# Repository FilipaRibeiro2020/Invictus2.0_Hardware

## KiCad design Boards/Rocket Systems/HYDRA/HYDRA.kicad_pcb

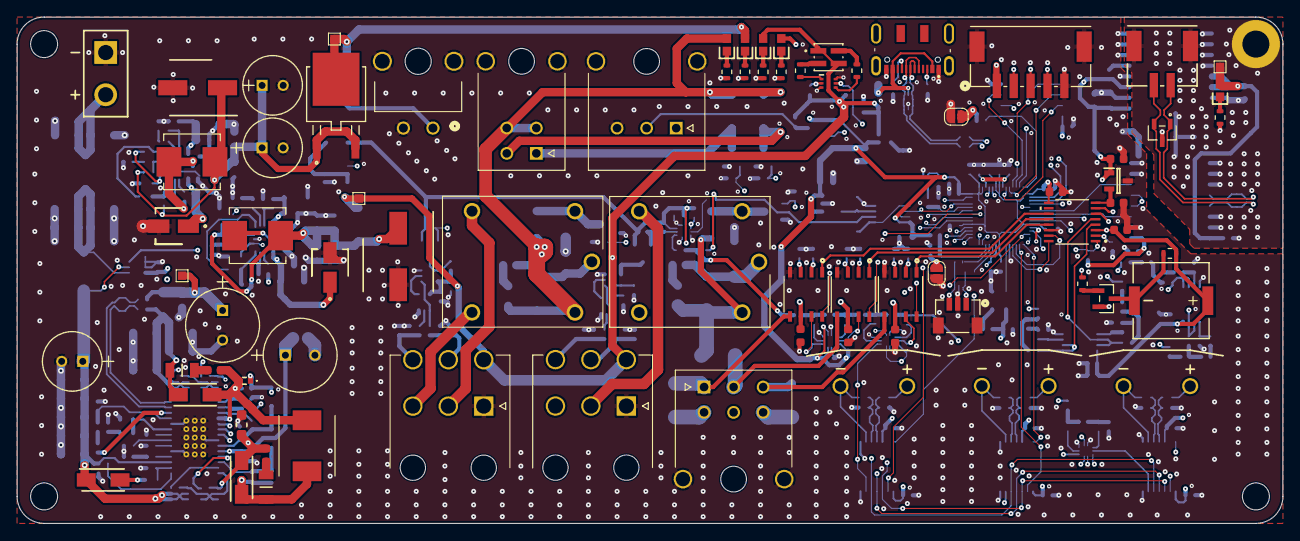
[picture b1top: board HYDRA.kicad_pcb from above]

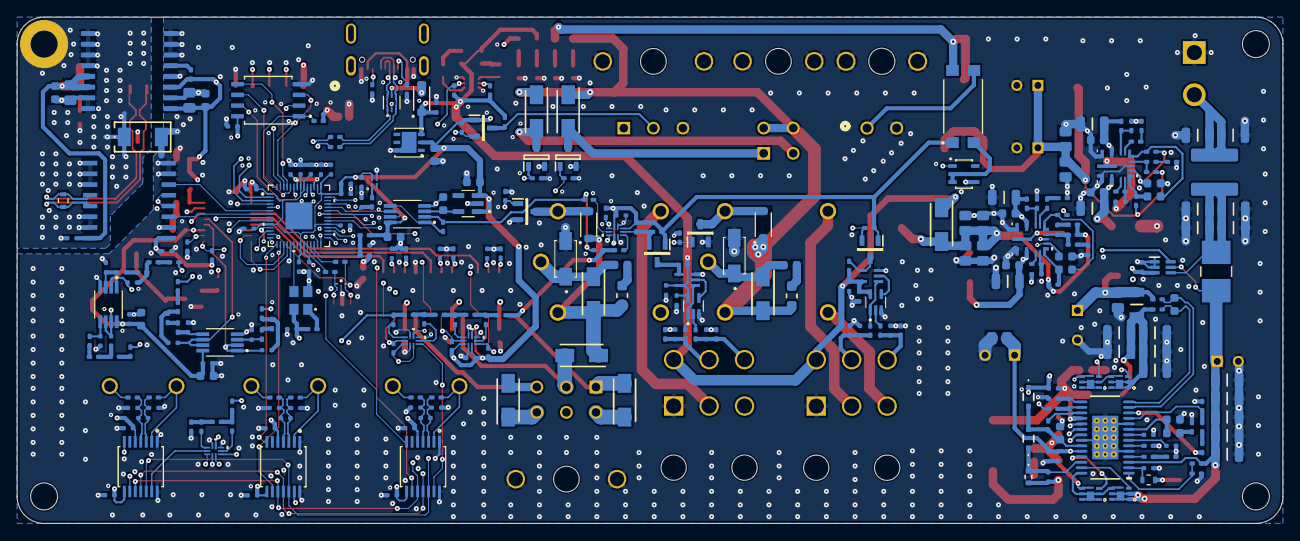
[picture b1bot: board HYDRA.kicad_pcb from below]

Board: 6 copper layers, 150.0 x 60.0 mm, 381 parts (302 on the bottom side), 234 nets.

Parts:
C1, C3, C6, C13: 1uF; Capacitor_0402
C1_comp1: 22nF; Capacitor_0603
C2, C4, C5, C7, C8, C9, C10, C11, C12, C14, C17, C62: 100nF; Capacitor_0402
C2_comp1: 270pF; Capacitor_0603
C15, C18, C20, C22, C23, C24, C25, C26, C27, C28, C30, C32, C33, C34, C36, C37, C41, C43, C44, C51, C54, C55, C57, C64, C66, C93, C94, C95: 100n; Capacitor_0402
C16: 4.7uF; Capacitor_0603
C19, C21, C29, C31, C40, C42, C45, C46, C47, C48: 10n; Capacitor_0402
C35, C38, C39, C56, C58, C60, C61, C63, C65: 1u; Capacitor_0603
C49, C50, C52, C53: 4.7n; Capacitor_0402
C59: 470n; Capacitor_0402
C67, C69, C72, C74: 2.2u; Capacitor_1206
C68: 68uF; CAP_WCAP-ATG8_6.3x11_WRE
C70, C71, C73, C75, C77: 4.7uF; Capacitor_1206
C76, C78: 470n; Capacitor_1206
C79, C88: 10uF; Capacitor_0805
C80, C86: 100nF; Capacitor_0603
C81: 300pF; C1808
C82, C83, C84, C85, C87: 10uF; Capacitor_1206
C89, C92: 3.3uF; Capacitor_0805
C90, C91: 180uF; CAP_WCAP-ATG8_8x11.5_WRE
C96, C97, C98: 1uF; Capacitor_0603
C99, C100: 100n; Capacitor_0603
CR1, CR2, CR3, CR4, CR5: VLMY1300-GS08; LEDC1608X100N
CR6: SP712-02HTG; SOT23-3_LTF
C_BIAS1, C_BIAS3: 1u; Capacitor_0603
C_BT1, C_BT2: 100n; Capacitor_0402
C_Boot2: 100nF; Capacitor_0402
C_FF1: 22p; Capacitor_0402
C_IN1, C_IN2, C_IN3, C_IN4: 4.7u; Capacitor_1206
C_IN-BLK1, C_IN-BLK2: 10u; Capacitor_4mm
C_IN_HFI1, C_IN_HFI2, C_IN_HFI3, C_IN_HFI4: 100n; Capacitor_0603
C_OUT1, C_OUT2, C_OUT6, C_OUT7, C_OUT8, C_OUT9: 22u; Capacitor_0805
C_OUT3, C_OUT4: 47u; CAP_WCAP-ATG8_6.3x11_WRE
C_OUT5: 100u; Capacitor-6.3mm
C_OUT10: 560u; Capacitor_8mm
C_Q1, C_Q2: 100pF; Capacitor_0603
C_VCC1, C_VCC3: 1u; Capacitor_0603
C_VIN1: 100nF; Capacitor_0402
C_bias2: 100nF; Capacitor_0402
C_boot1: 100nF; Capacitor_0402
C_cs1: 47pF; Capacitor_0402
C_isns1: 1uF; Capacitor_0603
C_slope1: 100pF; Capacitor_0402
C_ss1: 100nF; Capacitor_0402
C_vcc2: 1uF; Capacitor_0603
C_vosns1: 100pF; Capacitor_0402
D1: ESD122DMYR; DIO_ESD122DMYR
D2: SP3004-04XTG; SOT563_LTF
D3, D13, D14: PMEG2010ER; SODFL3517X110N
D4, D6, D7, D8, D9, D10, D11, D12, D17, D18, D19: RSX301L; DIOM5026X220N
D15, D16: SMAJ12A; DIOM4325X250N
D_Boot1, D_Boot2: BAS316,115; BAS316115
H1, H2, H4: MountingHole; MountingHole_3.2mm_M3_ISO7380
H3: MountingHole_Pad; MountingHole_3.2mm_M3_ISO7380_Pad
IC1: NSVT30010MXV6T1G; SOTFL50P160X60-6N
IC2: INA181A3QDCKRQ1; SOT65P210X110-6N
IC3: ISL21010CFH325Z-TK; SOT95P237X112-3N
J1: BM03B-SRSS-TBLFSN; CONN_BM03B-SRSS-TBLFSN_JST
J2: DX07S016JA1R1500; JAE_DX07S016JA1R1500
J3, J4: 26013116; MOLEX_26013116
J5: XT30UPB-F; XT30UPBF
J6: 5024430270; CONN_502443-02xx_MOL
J7: 1723163206; MOLEX_1723163206
J8: 1723163304; MOLEX_1723163304
J9: 1723103102; CONN02_1723103102_MOL
J10: 1723103103; MOLEX_1723103103
J11: 5024430570; CONN_502443-05xx_MOL
JP1, JP2: Jumper_2_Open; SolderJumper-2_P1.3mm_Open_RoundedPad1.0x1.5mm
K1: G3VM-31DR_TR05_; G3VM31DRTR05
K2, K3: PR12-12V-360-1C; RELAY_PR12-12V-360-1C
L1: 2.2u; SRP6030CA-2R2M
LS1: PKMCS0909E4000-R1; SPKR_PKMCS0909E4000-R1
L_SW1: 10u; Inductor-7.3mm-10u
L_SW2: 4.7uH; Inductor-7.2mm-4u7
L_SW3: 10uH; Inductor-7.3mm-10u
MCU1: RP2040; QFN56_7X7_RPI
Q1, Q2, Q7, Q8, Q9: BSS123; SOT96P237X111-3N
Q3, Q4, Q5, Q6: IRLHS6242TRPBF; QFN65P200X200X100-8N
Q10, Q11: PMV20XNER; SOT95P230X110-3N
R1: 62; RES_0603
R1_fb1: 20k; RES_0402
R1_mode1: 91k; RES_0402
R2, R3: 150; RES_0603
R2_fb1: 280k; RES_0402
R2_mode1, R24, R25, R26, R27, R32, R33, R35, R37, R40, R41, R46, R48, R50, R52: 2k; RES_0402
R3_fb1: 10; RES_0402
R4: 320; RES_0603
R5: 500; RES_0603
R6, R9, R18, R28, R29, R38, R45, R53, R54, R58, R61, R85, R86: 10k; RES_0402
R7, R8: 100; RES_0603
R10, R11: 1k; RES_0603
R12, R17, R21, R30, R31, R34, R36, R39, R42, R47, R49, R51, R55, R56, R57, R78: 1k; RES_0402
R13, R14: 27; RES_0402
R15, R16, R22, R23, R43, R44, R59, R60: 100; RES_0402
R19, R20: 5k1; RES_0402
R62, R63, R64, R66, R67, R68: 3k; RES_0402
R65, R69: 1k8; RES_0402
R70, R71, R72: 24k; RES_0402
R73: 5k6; RES_0402
R74, R75, R76: 750; RES_0402
R77: 36k; RES_0402
R79, R87, R88, R89, R92: 100k; RES_0402
R80: 120; RES_0603
R81: 100K; RES_0402
R82, R83, R84: 205K; RES_0402
R90, R91: 1k; RES_0805
R_BIAS1, R_BIAS2: 5; RES_0402
R_BT1: 50; RES_0402
R_BT2: 100; RES_0402
R_EN1: 390k; RES_0402
R_EN2: 56k; RES_0402
R_ENB1: 110k; RES_0402
R_ENB2: 56k; RES_0402
R_ENT1: 910k; RES_0402
R_ENT2: 470k; RES_0402
R_FBB1: 22k; RES_0402
R_FBB2: 100; RES_0402
R_FBT1: 12k; RES_0402
R_FBT2: 620; RES_0402
R_FBT3, R_FBT4: 100K; RES_0402
R_FF1: 1k; RES_0402
R_PG1, R_PG2: 100K; RES_0402
R_Q1, R_Q2: 10; RES_1206
R_RT1, R_RT3: 33k; RES_0402
R_RT2, R_RT4: 200; RES_0402
R_SENSE2: 8m; RES_2512
R_SNS1: 10m; RES_1206
R_VIN1: 10; RES_0603
R_comp1: 10k; RES_0402
R_cs1: 100; RES_0402
R_csg1: 100; RES_0402
R_good1: 10k; RES_0402
R_isns+1: 100; RES_0402
R_isns-1: 100; RES_0402
R_sense1: 8m; RES_0805
R_sync1: 84k5; RES_0402
TP2, TP3, TP5, TP6: TestPoint; TestPoint_Pad_1.0x1.0mm
U1: VLMKG3400-GS08; SMT_00-GS08_VIS
U2: BC846BLT1G; SOT-23_ONS
U3: W25Q128JVSIQ TR; SOIC_208MIL_WIN
U4: ST1L05APU33R; DFN_5APU33R_STM
U5, U6, U10, U11: NLAS5223BMNR2G; WQFN10_1P4X1P8_ONS
U7, U12, U16: MAX31856MUD+T; 21-0066J_14_MXM
U8, U15: SN74AHC1G86DCKRE4; SOT65P210X110-5N
U9, U17: 74AHC1G08SE-7; SOT65P210X110-5N
U13, U18, U19: MCP6002-E/MS; MSOP8_MC_MCH
U14: NCV8114ASN165T1G; SOT95P275X120-5N
U20: STLM20DD9F; UDFN-4L_STM
U21: AD5593RBRUZ; RU-16_ADI-L
U22: ISO1410BDW; DW0016B_L
U23, U25: LM61460AASQRJRRQ1; VQFN-HR14_RJR_TEX
U24: LM5175PWPR; PWP0028F_L
U26: UCC12050DVE; DVE0016A
U27: NCR321UX; TSOP6_SOT457_NEX
U28, U29, U30: DRV103H; DDA8-L
U31, U32, U33: ThermoConnector; Thermo Type K PCB Connector
U34: STPS15L45CB; DPAK_STM
XTAL1: ASE-12.000MHZ-LC-T; ASE24576MHZLCT
Z_Boot1, Z_Boot2: BZT52C8V2T-7; BZT52C8V2T7

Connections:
+1.65V: C39.1, U13.3 (VINA+), U14.5 (OUT)
+2.5V: C63.1, IC3.2 (VOUT), U21.8 (VREF)
+3.3V: C5.1, C6.1, C7.1, C8.1, C9.1, C10.1, C11.1, C12.1, C13.1, C14.1, C16.2, C17.1, C24.1, C25.1, C26.1, C27.2, C33.1, C34.2, C35.2, C38.1, C44.1, C51.2, C62.1, C64.1, C65.1, CR1.2, K1.1, MCU1.1 (IOVDD), MCU1.10 (IOVDD), MCU1.22 (IOVDD), MCU1.33 (IOVDD), MCU1.42 (IOVDD), MCU1.43 (ADC_AVDD), MCU1.44 (VREG_IN), MCU1.48 (USB_VDD), MCU1.49 (IOVDD), Q1.1 (G), Q2.1 (G), Q7.1 (G), R12.1, R18.2, R24.1, R25.1, R26.1, R27.1, R41.1, R45.1, R61.1, R79.1, R86.1, U3.8 (VCC), U4.2 (V0), U5.1 (VCC), U5.5 (NC1), U5.7 (NC2), U6.1 (VCC), U6.5 (NC1), U6.7 (NC2), U7.5 (AVDD), U7.8 (DVDD), U10.1 (VCC), U10.5 (NC1), U10.7 (NC2), U11.1 (VCC), U11.5 (NC1), U11.7 (NC2), U12.5 (AVDD), U12.8 (DVDD), U13.8 (VDD), U14.1 (IN), U14.3 (EN), U16.5 (AVDD), U16.8 (DVDD), U20.4 (VCC), U21.9 (VLOGIC), U22.1 (VCC1), XTAL1.4 (VDD)
+5V: C15.1, C18.1, C28.1, C32.1, C43.1, C54.1, C55.2, C56.1, C57.2, C58.1, C60.1, C61.1, C79.1, C80.1, CR3.2, D3.C, D8.1 (K), IC2.3 (VS), IC3.1 (VIN), J3.4, J4.4, LS1.1, R6.1, R9.2, R11.1, R38.1, R58.1, R81.1, R85.1, TP6.1, U1.1 (C_RED), U1.3 (C_Green), U4.3 (V1), U8.5 (VCC), U9.5 (VCC), U15.5 (VCC), U17.5 (VCC), U18.8 (VDD), U19.8 (VDD), U21.3 (VDD), U26.1 (EN), U26.3 (VINP)
+5VA: C66.2, C86.1, C88.1, CR2.2, TP3.1, U22.16 (VCC2), U26.13 (SEL), U26.14 (VISO)
+8.4V: CR4.2, J10.1, K1.4, TP2.1, U34.3 (K)
+12V: C89.2, C90.1, C91.1, C92.2, C96.1, C97.1, C98.1, CR5.2, C_bias2.1, C_vosns1.1, D9.1 (K), D10.1 (K), D11.1 (K), D12.1 (K), D13.C, D14.C, D17.2 (A), D18.2 (A), D19.1 (K), J7.4, J7.5, J7.6, J8.3, J8.4, J11.1, K2.A1, K3.A1, R3_fb1.1, R90.1, R91.1, R_SNS1.2, R_isns-1.1, TP5.1, U24.12 (VOSNS), U24.24 (BIAS), U28.6 (VS+), U29.6 (VS+), U30.6 (VS+)
/1~DRDY THERMO: MCU1.9 (GPIO7), U7.7 (~DRDY)
/2~DRDY THERMO: MCU1.15 (GPIO12), U12.7 (~DRDY)
/3~DRDY THERMO: MCU1.28 (GPIO17), U16.7 (~DRDY)
/Actuation Unit/CAM EN: MCU1.37 (GPIO25), U27.1 (VEN)
/Actuation Unit/CAM IN: J9.1, K1.3
/Actuation Unit/PWM HV: J10.2, Q7.3 (D), R85.2
/Actuation Unit/PWM LV: MCU1.5 (GPIO3), Q7.2 (S), R86.2
/Actuation Unit/QuickDisco N2: MCU1.34 (GPIO22), Q10.1 (G), R89.1
/Actuation Unit/QuickDisco N2 OUT: D12.2 (A), J8.1, Q10.3 (D)
/Actuation Unit/QuickDisco N2O: MCU1.32 (GPIO21), Q11.1 (G), R92.1
/Actuation Unit/QuickDisco N2O OUT: D19.2 (A), J8.2, Q11.3 (D)
/Actuation Unit/SOL_VALVE_1: MCU1.29 (GPIO18), U28.8 (INPUT)
/Actuation Unit/SOL_VALVE_1 DUTY: U21.11 (I/O5), U28.1 (DUTY_CYCLE)
/Actuation Unit/SOL_VALVE_1 OUT: D9.2 (A), J7.1, U28.5 (OUT)
/Actuation Unit/SOL_VALVE_1 ~FAULT: R25.2, U5.8 (IN2), U28.7 (STATUS_OK_FLAG)
/Actuation Unit/SOL_VALVE_2: MCU1.30 (GPIO19), U29.8 (INPUT)
/Actuation Unit/SOL_VALVE_2 DUTY: U21.12 (I/O6), U29.1 (DUTY_CYCLE)
/Actuation Unit/SOL_VALVE_2 OUT: D10.2 (A), J7.2, U29.5 (OUT)
/Actuation Unit/SOL_VALVE_2 ~FAULT: R24.2, U5.4 (IN1), U29.7 (STATUS_OK_FLAG)
/Actuation Unit/SOL_VALVE_3: MCU1.31 (GPIO20), U30.8 (INPUT)
/Actuation Unit/SOL_VALVE_3 DUTY: U21.13 (I/O7), U30.1 (DUTY_CYCLE)
/Actuation Unit/SOL_VALVE_3 OUT: D11.2 (A), J7.3, U30.5 (OUT)
/Actuation Unit/SOL_VALVE_3 ~FAULT: R41.2, U11.4 (IN1), U30.7 (STATUS_OK_FLAG)
/Actuation Unit/STVALVE_1: MCU1.35 (GPIO23), Q8.1 (G), R87.1
/Actuation Unit/STVALVE_1_CLOSED: J4.2, K3.NO
/Actuation Unit/STVALVE_1_OPEN: J4.3, K3.NC
/Actuation Unit/STVALVE_2: MCU1.36 (GPIO24), Q9.1 (G), R88.1
/Actuation Unit/STVALVE_2_CLOSED: J3.2, K2.NO
/Actuation Unit/STVALVE_2_OPEN: J3.3, K2.NC
/Buzzer: MCU1.4 (GPIO2), R10.2
/ENABLE_RS: MCU1.8 (GPIO6), U22.4 (~RE), U22.5 (DE)
/IO Connectors/PRESSURE1 Sense: J11.2, R62.1
/IO Connectors/PRESSURE2 Sense: J11.3, R63.1
/IO Connectors/PRESSURE3 Sense: J11.4, R64.1
/IO Connectors/RS_DN: CR6.1, J6.2, R80.1, U22.12 (A)
/IO Connectors/RS_DP: CR6.2, J6.1, R80.2, U22.13 (B)
/IO Connectors/SBVALVE_1_T2: C23.1, J4.6, R29.1, R31.2
/IO Connectors/SBVALVE_1_T3: C22.1, J4.5, R28.1, R30.2
/IO Connectors/SBVALVE_2_T2: C37.1, J3.6, R54.1, R57.2
/IO Connectors/SBVALVE_2_T3: C36.1, J3.5, R53.1, R56.2
/IO Connectors/THERMO1 DN: R23.2, U7.2 (BIAS), U31.2 (T-)
/IO Connectors/THERMO1 DP: R22.2, U31.1 (T+)
/IO Connectors/THERMO2 DN: R44.2, U12.2 (BIAS), U32.2 (T-)
/IO Connectors/THERMO2 DP: R43.2, U32.1 (T+)
/IO Connectors/THERMO3 DN: R60.2, U16.2 (BIAS), U33.2 (T-)
/IO Connectors/THERMO3 DP: R59.2, U33.1 (T+)
/MISO SPI: MCU1.11 (GPIO8), U7.11 (SDO), U12.11 (SDO), U16.11 (SDO)
/MOSI SPI: MCU1.14 (GPIO11), U7.12 (SDI), U12.12 (SDI), U16.12 (SDI)
/PCB Temperature Sense: C59.2, MCU1.38 (GPIO26_ADC0), R77.1
/Power Unit/DC.DC2 PGOOD: C_BIAS1.2, R_PG1.2, U23.5 (PGOOD)
/Power Unit/DC.DC2 VCC: C_VCC1.1, R_PG1.1, U23.2 (VCC)
/Power Unit/DC.DC3 PGOOD: C_BIAS3.2, R_PG2.2, U25.5 (PGOOD)
/Power Unit/DC.DC3 VCC: C_VCC3.1, R_PG2.1, U25.2 (VCC)
/Power Unit/HDRV1: Q3.3, U24.27 (HDRV1)
/Power Unit/HDRV2: Q5.3, U24.19 (HDRV2)
/Power Unit/ISNS+: C_isns1.2, R_isns+1.2, U24.14 (ISNS+)
/Power Unit/ISNS-: C_isns1.1, R_isns-1.2, U24.13 (ISNS-)
/Power Unit/LDRV1: Q4.3, U24.25 (LDRV1)
/Power Unit/LDRV2: Q6.3, U24.21 (LDRV2)
/Power Unit/SENSE: C_Q1.2, D6.2 (A), Q4.4, Q4.8, Q6.4, Q6.8, R_cs1.1, R_sense1.2
/Power Unit/SW1: C_Boot2.2, D6.1 (K), L_SW2.1, Q3.4, Q3.8, Q4.1, Q4.2, Q4.5, Q4.6, Q4.7, R_Q1.1, U24.28 (SW1), Z_Boot1.2 (A)
/Power Unit/SW2: C_Q2.2, C_boot1.2, D7.2 (A), L_SW2.2, Q5.4, Q5.8, Q6.1, Q6.2, Q6.5, Q6.6, Q6.7, U24.18 (SW2), Z_Boot2.2 (A)
/Power Unit/VBAT DP: C72.1, C74.1, C76.1, C78.1, IC2.4 (IN+), L1.2, R_SENSE2.1
/READ_RS: MCU1.7 (GPIO5), U22.3 (R)
/RP2040 Standard/CLK SWD: D1.2, J1.1, R15.1
/RP2040 Standard/Crystal: MCU1.20 (XIN), XTAL1.3 (OUTPUT)
/RP2040 Standard/GP14/I2C1 SDA: MCU1.17 (GPIO14), U21.15 (SDA)
/RP2040 Standard/GP15/I2C1 SCL: MCU1.18 (GPIO15), U21.16 (SCL)
/RP2040 Standard/GPIO16: MCU1.27 (GPIO16), R79.2, U21.1 (*RESET)
/RP2040 Standard/MCU SCLK SPI: MCU1.52 (QSPI_SCLK), U3.6 (CLK)
/RP2040 Standard/MCU SD0 SPI: MCU1.53 (QSPI_SD0), U3.5 (DI(IO0))
/RP2040 Standard/MCU SD1 SPI: MCU1.55 (QSPI_SD1), U3.2 (DO(IO1))
/RP2040 Standard/MCU SD2 SPI: MCU1.54 (QSPI_SD2), U3.3 (/WP(IO2))
/RP2040 Standard/MCU SD3 SPI: MCU1.51 (QSPI_SD3), U3.7 (/HOLD_/RESET)
/RP2040 Standard/MCU ~CS SPI: MCU1.56 (QSPI_SS), R21.2, U3.1 (/CS)
/RP2040 Standard/SWD: D1.3, J1.3, R16.1
/RP2040 Standard/USB_D+: MCU1.47 (USB_DP), R13.2
/RP2040 Standard/USB_D-: MCU1.46 (USB_DM), R14.2
/RP2040 Standard/USB_DN: D2.3 (IO2), D2.4 (IO3), J2.5 (D-), J2.8 (D-), R14.1
/RP2040 Standard/USB_DP: D2.1 (IO1), D2.6 (IO4), J2.6 (D+), J2.7 (D+), R13.1
/RP2040 Standard/~RST: JP1.2 (B), R17.1
/RP2040 Standard/~USB_BOOT: JP2.2 (B), R21.1
/SCK SPI: MCU1.13 (GPIO10), U7.10 (SCK), U12.10 (SCK), U16.10 (SCK)
/Sensor Unit/1~FAULT THERMO: U7.13 (~FAULT), U10.4 (IN1)
/Sensor Unit/2~FAULT THERMO: U10.8 (IN2), U12.13 (~FAULT)
/Sensor Unit/3~FAULT THERMO: U11.8 (IN2), U16.13 (~FAULT)
/Sensor Unit/ADC1 Sense: C45.2, U18.1 (VOUTA), U18.2 (VINA-), U21.4 (I/O0)
/Sensor Unit/ADC2 Sense: C48.2, U18.6 (VINB-), U18.7 (VOUTB), U21.5 (I/O1)
/Sensor Unit/ADC3 Sense: C46.2, U19.1 (VOUTA), U19.2 (VINA-), U21.6 (I/O2)
/Sensor Unit/ADC4 Sense: C47.2, U19.6 (VINB-), U19.7 (VOUTB), U21.7 (I/O3)
/Sensor Unit/BUFF FB: MCU1.39 (GPIO27_ADC1), U13.6 (VINB-), U13.7 (VOUTB)
/Sensor Unit/BUFF IN: R55.1, U13.1 (VOUTA), U13.5 (VINB+)
/Sensor Unit/SBVALVE_1_SIG: Q1.2 (S), R26.2, R45.2, U6.4 (IN1)
/Sensor Unit/SBVALVE_1_STATE: Q1.3 (D), R38.2, U9.4 (Y)
/Sensor Unit/SBVALVE_2_SIG: Q2.2 (S), R27.2, R61.2, U6.8 (IN2)
/Sensor Unit/SBVALVE_2_STATE: Q2.3 (D), R58.2, U17.4 (Y)
/Sensor Unit/V0: R33.1, U10.3 (COM1)
/Sensor Unit/V1: R35.1, U10.9 (COM2)
/Sensor Unit/V2: R37.1, U11.3 (COM1)
/Sensor Unit/V3: R40.1, U11.9 (COM2)
/Sensor Unit/V4: R46.1, U5.3 (COM1)
/Sensor Unit/V5: R48.1, U5.9 (COM2)
/Sensor Unit/V6: R50.1, U6.3 (COM1)
/Sensor Unit/V7: R52.1, U6.9 (COM2)
/Sensor Unit/VBAT Sense: IC2.6 (OUT), R65.1
/WRITE_RS: MCU1.6 (GPIO4), U22.6 (D)
/~CS THERMO1 SPI: MCU1.12 (GPIO9), U7.9 (~CS)
/~CS THERMO2 SPI: MCU1.16 (GPIO13), U12.9 (~CS)
/~CS THERMO3 SPI: MCU1.41 (GPIO29_ADC3), U16.9 (~CS)
/~Green Status: IC1.2 (B2), MCU1.3 (GPIO1), R6.2
/~Red Status: IC1.5 (B1), MCU1.2 (GPIO0), R9.1
AGND: C66.1, C81.1, C86.2, C88.2, CR6.3, H3.1, J6.3 (MP1), J6.4 (MP2), R2.1, U22.9 (GND2), U22.10 (NC), U22.11 (NC), U22.14 (NC), U22.15 (GND2), U26.9 (GNDS), U26.10 (NCS), U26.11 (NCS), U26.12 (NCS), U26.15 (GNDS), U26.16 (NCS)
GND: C1.2, C2.1, C2_comp1.1, C3.2, C4.1, C5.2, C6.2, C7.2, C8.2, C9.2, C10.2, C11.2, C12.2, C13.2, C14.2, C15.2, C16.1, C17.2, C18.2, C19.1, C21.2, C22.2, C23.2, C24.2, C25.2, C26.2, C27.1, C28.2, C29.1, C31.2, C32.2, C33.2, C34.1, C35.1, C36.2, C37.2, C38.2, C39.2, C40.1, C42.2, C43.2, C44.2, C49.2, C50.2, C51.1, C52.2, C53.2, C54.2, C55.1, C56.2, C57.1, C58.2, C59.1, C60.2, C61.2, C62.2, C63.2, C64.2, C65.2, C67.2, C68.2, C69.2, C70.1, C71.1, C72.2, C73.1, C74.2, C75.1, C76.2, C77.1, C78.2, C79.2, C80.2, C81.2, C82.1, C83.1, C84.1, C85.1, C87.1, C89.1, C90.2, C91.2, C92.1, C93.2, C94.2, C95.2, C96.2, C97.2, C98.2, C_IN1.2, C_IN2.2, C_IN3.2, C_IN4.2, C_IN-BLK1.2, C_IN-BLK2.2, C_IN_HFI1.2, C_IN_HFI2.2, C_IN_HFI3.2, C_IN_HFI4.2, C_OUT1.2, C_OUT2.2, C_OUT3.2, C_OUT4.2, C_OUT5.2, C_OUT6.2, C_OUT7.2, C_OUT8.2, C_OUT9.2, C_OUT10.2, C_VCC1.2, C_VCC3.2, C_VIN1.2, C_bias2.2, C_slope1.2, C_ss1.2, C_vcc2.2, C_vosns1.2, D1.1, D2.2 (GND), D15.A, D16.A, IC1.3 (C1), IC1.6 (C2), IC2.1 (REF), IC2.2 (GND), IC3.3 (GND), J1.2, J1.4 (EP), J1.5 (EP), J2.1 (GND), J2.12 (GND), J3.1, J4.1, J5.1, J7.S1 (SHIELD1), J7.S2 (SHIELD2), J8.S1 (SHIELD1), J8.S2 (SHIELD2), J9.2, J9.3 (SHIELD1), J9.4 (SHIELD2), J10.3, J10.S1 (SHIELD1), J10.S2 (SHIELD2), J11.5, J11.6, J11.7, JP1.1 (A), JP2.1 (A), MCU1.19 (TESTEN), MCU1.57 (GND), Q8.2 (S), Q9.2 (S), Q10.2 (S), Q11.2 (S), R1.1, R1_fb1.2, R2_mode1.1, R3.1, R4.1, R5.1, R19.1, R20.2, R28.2, R29.2, R32.1, R53.2, R54.2, R78.1, R82.2, R83.2, R84.2, R87.2, R88.2, R89.2, R92.2, R_EN2.2, R_ENB1.1, R_ENB2.1, R_FBB1.1, R_FBT1.2, R_RT2.1, R_RT4.1, R_comp1.2, R_csg1.1, R_sense1.1, R_sync1.2, U2.2 (E), U3.4 (GND), U4.6 (GND), U4.7 (GND), U5.2 (NO1), U5.6 (GND), U5.10 (NO2), U6.2 (NO1), U6.6 (GND), U6.10 (NO2), U7.1 (AGND), U7.14 (DGND), U8.3 (GND), U9.3 (GND), U10.2 (NO1), U10.6 (GND), U10.10 (NO2), U11.2 (NO1), U11.6 (GND), U11.10 (NO2), U12.1 (AGND), U12.14 (DGND), U13.4 (VSS), U14.2 (GND), U15.3 (GND), U16.1 (AGND), U16.14 (DGND), U17.3 (GND), U18.4 (VSS), U19.4 (VSS), U20.3 (GND), U21.14 (GND), U22.2 (GND1), U22.7 (NC), U22.8 (GND1), U23.3 (AGND), U23.9 (PGND1), U23.11 (PGND2), U24.5 (DITH), U24.10 (AGND), U24.22 (PGND), U24.29 (PAD), U24.V, U25.3 (AGND), U25.9 (PGND1), U25.11 (PGND2), U26.2 (GNDP), U26.4 (SYNC), U26.6 (NCP), U26.7 (NCP), U26.8 (NCP), U27.4 (GND), U28.4 (GND), U29.4 (GND), U30.4 (GND), XTAL1.2 (GND/CASE)
unnamed: C1_comp1.1, R_comp1.1
unnamed: C45.1, R65.2, R69.1
unnamed: C46.1, R67.2, R70.1
unnamed: C47.1, R68.2, R71.1
unnamed: C48.1, R66.2, R72.1
unnamed: C99.2, R90.2
unnamed: C100.2, R91.2
unnamed: CR1.1, R1.2
unnamed: CR2.1, R2.2
unnamed: CR3.1, R3.2
unnamed: CR4.1, R4.2
unnamed: CR5.1, R5.2
unnamed: C_FF1.1, R_FF1.2
unnamed: C_OUT1.1, C_OUT2.1, C_OUT3.1, C_OUT4.1, C_OUT5.1, L_SW1.2, R_BIAS1.2, R_FBT3.1, U34.1, U34.2
unnamed: C_Q1.1, R_Q1.2
unnamed: C_Q2.1, R_Q2.2
unnamed: D4.2 (A), R_VIN1.1
unnamed: C82.2, C83.2, C84.2, C85.2, C87.2, D7.1 (K), Q5.1, Q5.2, Q5.5, Q5.6, Q5.7, R_Q2.1, R_SNS1.1, R_isns+1.1
unnamed: C_OUT6.1, C_OUT7.1, C_OUT8.1, C_OUT9.1, C_OUT10.1, D8.2 (A), L_SW3.2, R_BIAS2.2, R_FBT4.1, R_FF1.1
unnamed: C99.1, D15.C, D17.1 (K), K3.COM
unnamed: C100.1, D16.C, D18.1 (K), K2.COM
unnamed: C_vcc2.1, D_Boot1.2 (A), D_Boot2.2 (A), R_good1.2, U24.23 (VCC)
unnamed: C_Boot2.1, D_Boot1.1 (K), U24.26 (BOOT1), Z_Boot1.1 (K)
unnamed: C_boot1.1, D_Boot2.1 (K), U24.20 (BOOT2), Z_Boot2.1 (K)
unnamed: IC1.4 (E1), R8.1
unnamed: IC1.1 (E2), R7.2
unnamed: J2.3 (CC1), R19.2
unnamed: J2.9 (CC2), R20.1
unnamed: K1.2, U27.2 (IOUT), U27.3 (IOUT), U27.5 (IOUT)
unnamed: C1.1, MCU1.26 (RUN), R12.2, R17.2
unnamed: MCU1.24 (SWCLK), R15.2
unnamed: MCU1.25 (SWD), R16.2
unnamed: C2.2, C3.1, C4.2, MCU1.23 (DVDD), MCU1.45 (VREG_VOUT), MCU1.50 (DVDD)
unnamed: D13.A, K3.A2, Q8.3 (D)
unnamed: D14.A, K2.A2, Q9.3 (D)
unnamed: R1_mode1.1, R2_mode1.2
unnamed: R2_fb1.1, R3_fb1.2
unnamed: R32.2, R33.2, R34.2
unnamed: R34.1, R35.2, R36.2
unnamed: R36.1, R37.2, R39.2
unnamed: R39.1, R40.2, R42.2
unnamed: R42.1, R46.2, R47.2
unnamed: R47.1, R48.2, R49.1
unnamed: R49.2, R50.2, R51.2
unnamed: R62.2, R66.1
unnamed: R63.2, R67.1
unnamed: R64.2, R68.1
unnamed: R69.2, R73.1
unnamed: R70.2, R74.1
unnamed: R71.2, R75.1
unnamed: R72.2, R76.1
unnamed: R_FBB1.2, R_FBB2.1
unnamed: R_FBT1.1, R_FBT2.2
unnamed: R_RT1.1, R_RT2.2
unnamed: R_RT3.1, R_RT4.2
unnamed: R7.1, U1.2 (A_Green)
unnamed: R8.2, U1.4 (A_Red)
unnamed: R10.1, U2.1 (B)
unnamed: LS1.2, R11.2, U2.3 (C)
unnamed: C19.2, C20.1, R22.1, U7.4 (T+)
unnamed: C20.2, C21.1, R23.1, U7.3 (T-)
unnamed: R30.1, U8.1 (A), U9.1 (A)
unnamed: R31.1, U8.2 (B)
unnamed: U8.4 (Y), U9.2 (B)
unnamed: C29.2, C30.1, R43.1, U12.4 (T+)
unnamed: C30.2, C31.1, R44.1, U12.3 (T-)
unnamed: R51.1, R52.2, R55.2, U13.2 (VINA-)
unnamed: R56.1, U15.1 (A), U17.1 (A)
unnamed: R57.1, U15.2 (B)
unnamed: U15.4 (Y), U17.2 (B)
unnamed: C40.2, C41.1, R59.1, U16.4 (T+)
unnamed: C41.2, C42.1, R60.1, U16.3 (T-)
unnamed: C52.1, R73.2, U18.3 (VINA+)
unnamed: C50.1, R76.2, U18.5 (VINB+)
unnamed: C53.1, R74.2, U19.3 (VINA+)
unnamed: C49.1, R75.2, U19.5 (VINB+)
unnamed: R77.2, U20.1 (VOUT)
unnamed: R78.2, U21.2 (A0)
unnamed: C_BIAS1.1, R_BIAS1.1, U23.1 (BIAS)
unnamed: C_BT1.2, R_BT1.1, U23.14 (CBOOT)
unnamed: R_ENB1.2, R_ENT1.1, U23.7 (EN/SYNC)
unnamed: R_FBT2.1, R_FBT3.2, U23.4 (FB)
unnamed: R_BT1.2, U23.13 (RBOOT)
unnamed: R_RT1.2, U23.6 (RT)
unnamed: C_BT1.1, L_SW1.1, U23.10 (SW)
unnamed: C1_comp1.2, C2_comp1.2, U24.9 (COMP)
unnamed: C_cs1.2, R_cs1.2, U24.16 (CS)
unnamed: C_cs1.1, R_csg1.2, U24.15 (CSG)
unnamed: R_EN1.2, R_EN2.1, U24.1 (EN)
unnamed: R1_fb1.1, R2_fb1.2, U24.11 (FB)
unnamed: R1_mode1.2, U24.4 (MODE)
unnamed: R_good1.1, U24.17 (PGOOD)
unnamed: R_sync1.1, U24.6 (RT_SYNC)
unnamed: C_slope1.1, U24.7 (SLOPE)
unnamed: C_ss1.1, U24.8 (SS)
unnamed: C_VIN1.1, R_VIN1.2, U24.2 (VIN)
unnamed: C_BIAS3.1, R_BIAS2.1, U25.1 (BIAS)
unnamed: C_BT2.2, R_BT2.1, U25.14 (CBOOT)
unnamed: R_ENB2.2, R_ENT2.1, U25.7 (EN/SYNC)
unnamed: C_FF1.2, R_FBB2.2, R_FBT4.2, U25.4 (FB)
unnamed: R_BT2.2, U25.13 (RBOOT)
unnamed: R_RT3.2, U25.6 (RT)
unnamed: C_BT2.1, L_SW3.1, U25.10 (SW)
unnamed: R81.2, U26.5 (FAULT_N)
unnamed: C94.1, U28.2 (DELAY)
unnamed: R83.1, U28.3 (OSC_FREQ)
unnamed: C95.1, U29.2 (DELAY)
unnamed: R84.1, U29.3 (OSC_FREQ)
unnamed: C93.1, U30.2 (DELAY)
unnamed: R82.1, U30.3 (OSC_FREQ)
unnamed: R18.1, XTAL1.1 (TRI-STATE(STBY))
VBAT: C67.1, C69.1, J5.2, L1.1
VBUS: D2.5 (VCC), D3.A, J2.2 (VBUS), J2.11 (VBUS)
VDC: C68.1, C70.2, C71.2, C73.2, C75.2, C77.2, C_IN1.1, C_IN2.1, C_IN3.1, C_IN4.1, C_IN-BLK1.1, C_IN-BLK2.1, C_IN_HFI1.1, C_IN_HFI2.1, C_IN_HFI3.1, C_IN_HFI4.1, D4.1 (K), IC2.5 (IN-), Q3.1, Q3.2, Q3.5, Q3.6, Q3.7, R_EN1.1, R_ENT1.2, R_ENT2.2, R_SENSE2.2, U23.8 (VIN1), U23.12 (VIN2), U24.3 (VINSNS), U25.8 (VIN1), U25.12 (VIN2)
